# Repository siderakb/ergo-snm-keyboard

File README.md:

# ErgoSNM Keyboard

*ErgoSNM* \- a split ergonomic keyboard integrated with a trackball, designed to encourage people to leave their mouse behind.

- 64 keys in total.
    - Left half 29 + 6 keys.
    - Right half 29 keys + trackball.
- Cherry MX style switches, hot-swap available.
- USB Type-C.
- Column-staggered layout.
- The trackball can replace all mouse operations, allowing your right hand to stay on the *home row*.
    - Cursor movement and scrolling.
    - With the Combos feature:
        - *J*+*K* performs the left click
        - *K*+*L* performs the right click
        - *J*+*L* performs the middle click.

Introduction Video:

| Rev   | MCU                       | Note                                     | Video                                               |
| ----- | ------------------------- | ---------------------------------------- | --------------------------------------------------- |
| `1.x` | Pro Micro (ATmega32U4)    | Experimental version                     |                                                     |
| `2.x` | RaspberryPi **RP2040**    | The first version suitable for daily use | [demo](https://youtu.be/1BXKdrCFn6c)                |
| `3.x` | Nordic **nRF52840** (E73) | First wireless experimental version      | [demo](https://www.youtube.com/watch?v=TtJiaOGiEaQ) |
| `4.x` | ???                       | ⚡In progress                             |                                                     |

Build guide and more information can be found in the [📖Docs](https://siderakb.ziteh.dev/docs/ergosnm/intro)

## Clone

```bash
git clone --recurse-submodules https://github.com/siderakb/ergo-snm-keyboard.git
```

If `key-switches.pretty` folder is empty, run:

```bash
git submodule update --init --recursive
```

## Firmware

- Vial QMK: [siderakb/vial-qmk](https://github.com/siderakb/vial-qmk/tree/siderakb/main/keyboards/siderakb/ergosnm) (*siderakb/main* branch)
- nRF: [siderakb/ergo-snm-nrf-firmware](https://github.com/siderakb/ergo-snm-nrf-firmware)

## License

Hardware available under the [CERN-OHL-P v2](/LICENSE) permissive license.

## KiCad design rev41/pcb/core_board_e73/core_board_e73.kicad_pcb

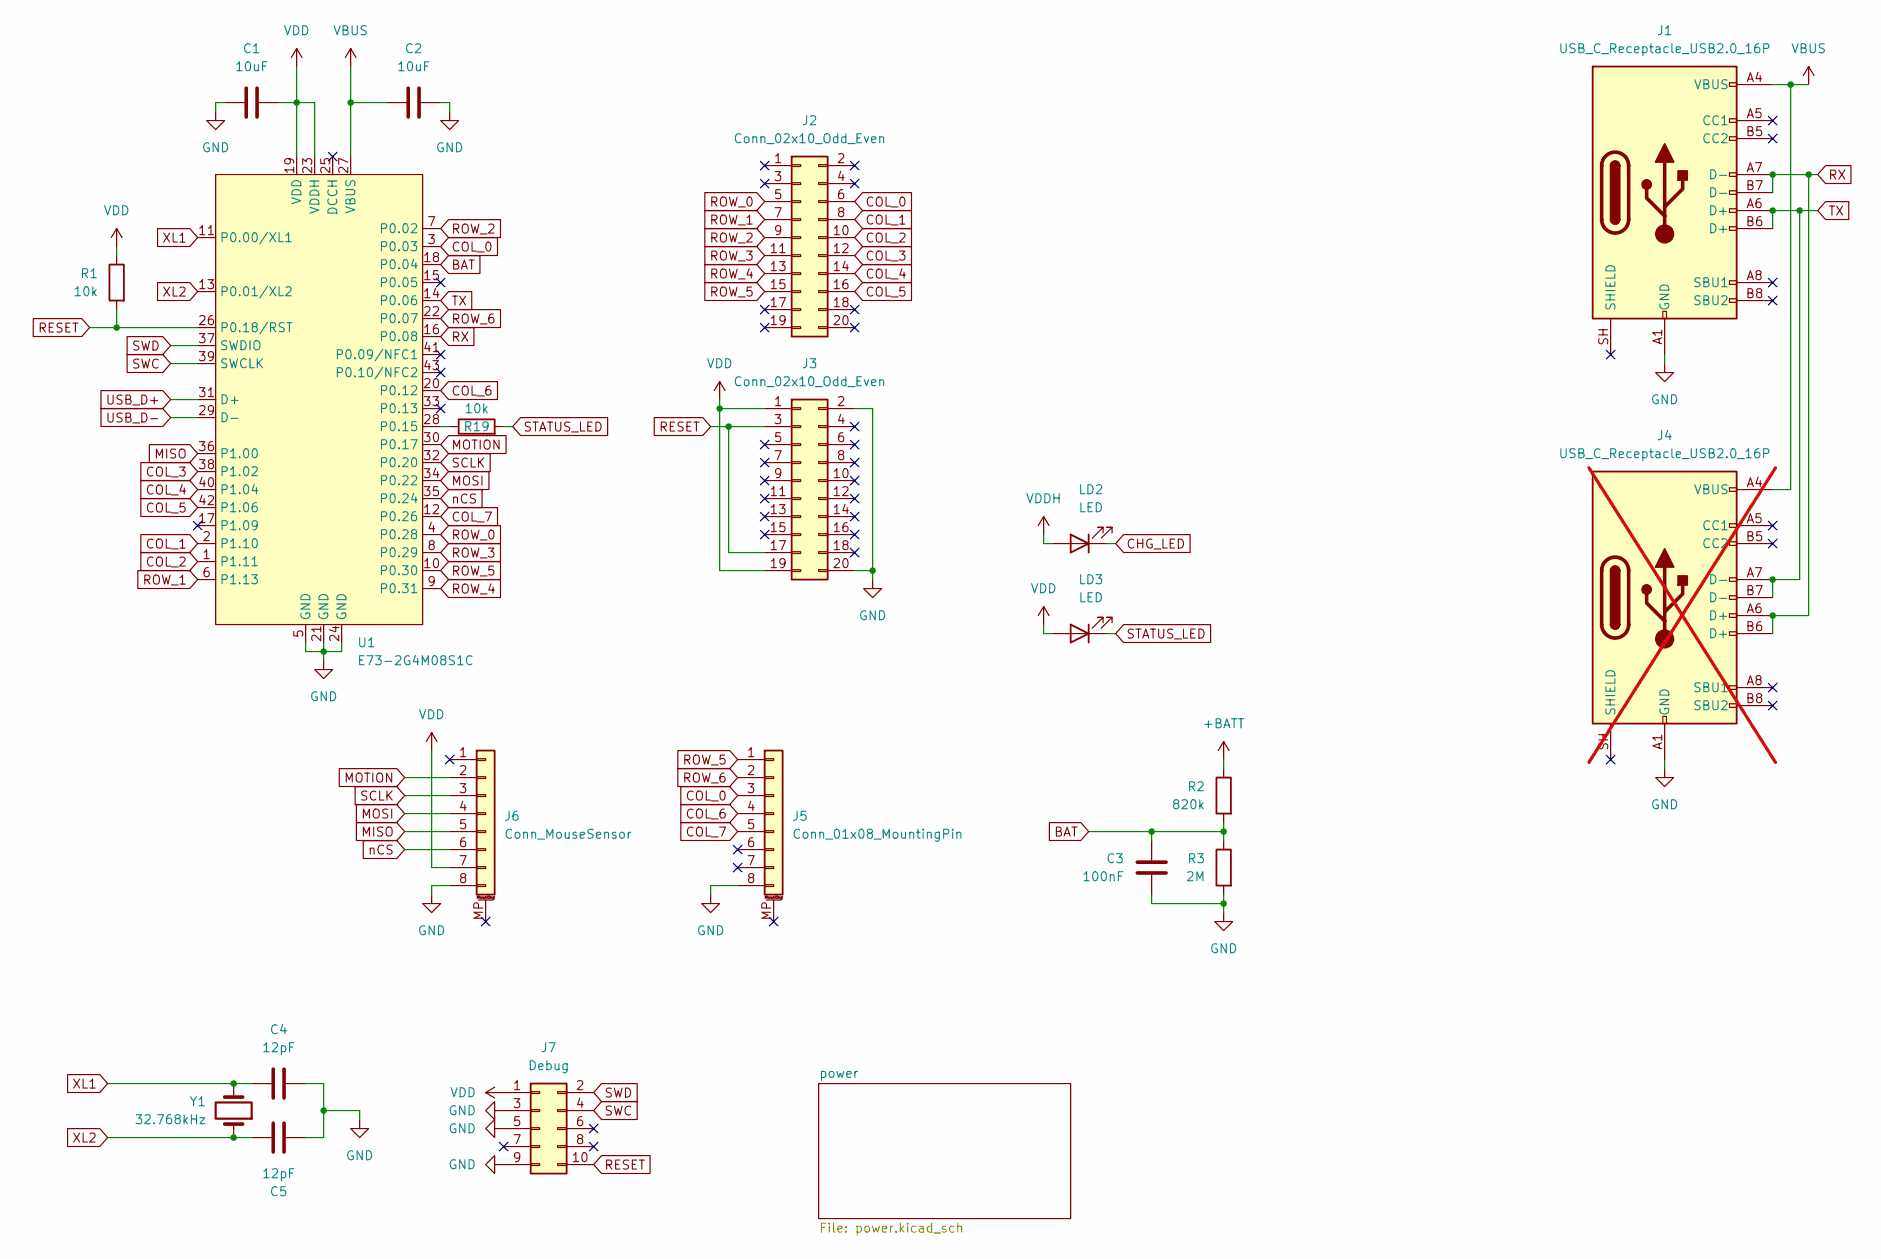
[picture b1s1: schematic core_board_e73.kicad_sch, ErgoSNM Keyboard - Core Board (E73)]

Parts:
C1, C2: 10uF; C_0603_1608Metric; MFR. Part # CL10A106KP8NNNC; JLCPCB Part # C19702
C3: 100nF; C_0402_1005Metric; MFR. Part # CL05B104KO5NNNC; JLCPCB Part # C1525
C4, C5: 12pF; C_0402_1005Metric; MFR. Part # 0402CG120J500NT; JLCPCB Part # C1547
J1: USB_C_Receptacle_USB2.0_16P; USB_C_Receptacle_HRO_TYPE-C-31-M-12; MFR. Part # TYPE-C-31-M-12; JLCPCB Part # C165948
J2, J3: Conn_02x10_Odd_Even; PinHeader_2x10_P1.27mm_Vertical
J4: USB_C_Receptacle_USB2.0_16P; USB_C_Receptacle_HRO_TYPE-C-31-M-12; MFR. Part # TYPE-C-31-M-12; JLCPCB Part # C165948; not fitted
J5: Conn_01x08_MountingPin; FPC_8P_0.5mm_AFC01-S08FCA-00; MFR. Part # FPC-05F-8PH20; JLCPCB Part # C2856797
J6: Conn_MouseSensor; FPC_8P_0.5mm_AFC01-S08FCA-00; MFR. Part # FPC-05F-8PH20; JLCPCB Part # C2856797
J7: Debug; PinHeader_2x05_P1.27mm_Vertical
LD2, LD3: LED; LED_0603_1608Metric_Pad1.05x0.95mm_HandSolder
R1, R19: 10k; R_0402_1005Metric; MFR. Part # 0402WGF1002TCE; JLCPCB Part # C25744
R2: 820k; R_0402_1005Metric; MFR. Part # FRC0402F8203TS; JLCPCB Part # C2909386
R3: 2M; R_0402_1005Metric; MFR. Part # 0402WGF2004TCE; JLCPCB Part # C11512
U1: E73-2G4M08S1C; E73-2G4M08S1C-52840_Hand; MFR. Part # E73-2G4M08S1C; JLCPCB Part # C356849
Y1: 32.768kHz; Crystal_SMD_3215-2Pin_3.2x1.5mm; MFR. Part # Q13FC13500004; JLCPCB Part # C32346

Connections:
+BATT: R2.1; also elsewhere on the board
BAT: C3.1, R2.2, R3.1, U1.18 (P0.04)
CHG_LED: LD2.1 (K); also elsewhere on the board
COL_0: J2.6, J5.3, U1.3 (P0.03)
COL_1: J2.8, U1.2 (P1.10)
COL_2: J2.10, U1.1 (P1.11)
COL_3: J2.12, U1.38 (P1.02)
COL_4: J2.14, U1.40 (P1.04)
COL_5: J2.16, U1.42 (P1.06)
COL_6: J5.4, U1.20 (P0.12)
COL_7: J5.5, U1.12 (P0.26)
GND: C1.1, C2.2, C3.2, C4.2, C5.1, J1.A1 (GND), J1.A12 (GND), J1.B1 (GND), J1.B12 (GND), J3.2, J3.20, J4.A1 (GND), J4.A12 (GND), J4.B1 (GND), J4.B12 (GND), J5.8, J6.8, J7.3, J7.5, J7.9, R3.2, U1.5 (GND), U1.21 (GND), U1.24 (GND); also elsewhere on the board
MISO: J6.5, U1.36 (P1.00)
MOSI: J6.4, U1.34 (P0.22)
MOTION: J6.2, U1.30 (P0.17)
unnamed: R19.1, U1.28 (P0.15)
RESET: J3.3, J3.17, J7.10, R1.2, U1.26 (P0.18/RST)
ROW_0: J2.5, U1.4 (P0.28)
ROW_1: J2.7, U1.6 (P1.13)
ROW_2: J2.9, U1.7 (P0.02)
ROW_3: J2.11, U1.8 (P0.29)
ROW_4: J2.13, U1.9 (P0.31)
ROW_5: J2.15, J5.1, U1.10 (P0.30)
ROW_6: J5.2, U1.22 (P0.07)
RX: J1.A7 (D-), J1.B7 (D-), J4.A6 (D+), J4.B6 (D+), U1.16 (P0.08)
SCLK: J6.3, U1.32 (P0.20)
STATUS_LED: LD3.1 (K), R19.2
SWC: J7.4, U1.39 (SWCLK)
SWD: J7.2, U1.37 (SWDIO)
TX: J1.A6 (D+), J1.B6 (D+), J4.A7 (D-), J4.B7 (D-), U1.14 (P0.06)
USB_D+: U1.31 (D+); also elsewhere on the board
USB_D-: U1.29 (D-); also elsewhere on the board
VBUS: C2.1, J1.A4 (VBUS), J1.A9 (VBUS), J1.B4 (VBUS), J1.B9 (VBUS), J4.A4 (VBUS), J4.A9 (VBUS), J4.B4 (VBUS), J4.B9 (VBUS), U1.27 (VBUS); also elsewhere on the board
VDD: C1.2, J3.1, J3.19, J6.7, J7.1, LD3.2 (A), R1.1, U1.19 (VDD), U1.23 (VDDH); also elsewhere on the board
VDDH: LD2.2 (A); also elsewhere on the board
XL1: C4.1, U1.11 (P0.00/XL1), Y1.2
XL2: C5.2, U1.13 (P0.01/XL2), Y1.1
nCS: J6.6, U1.35 (P0.24)

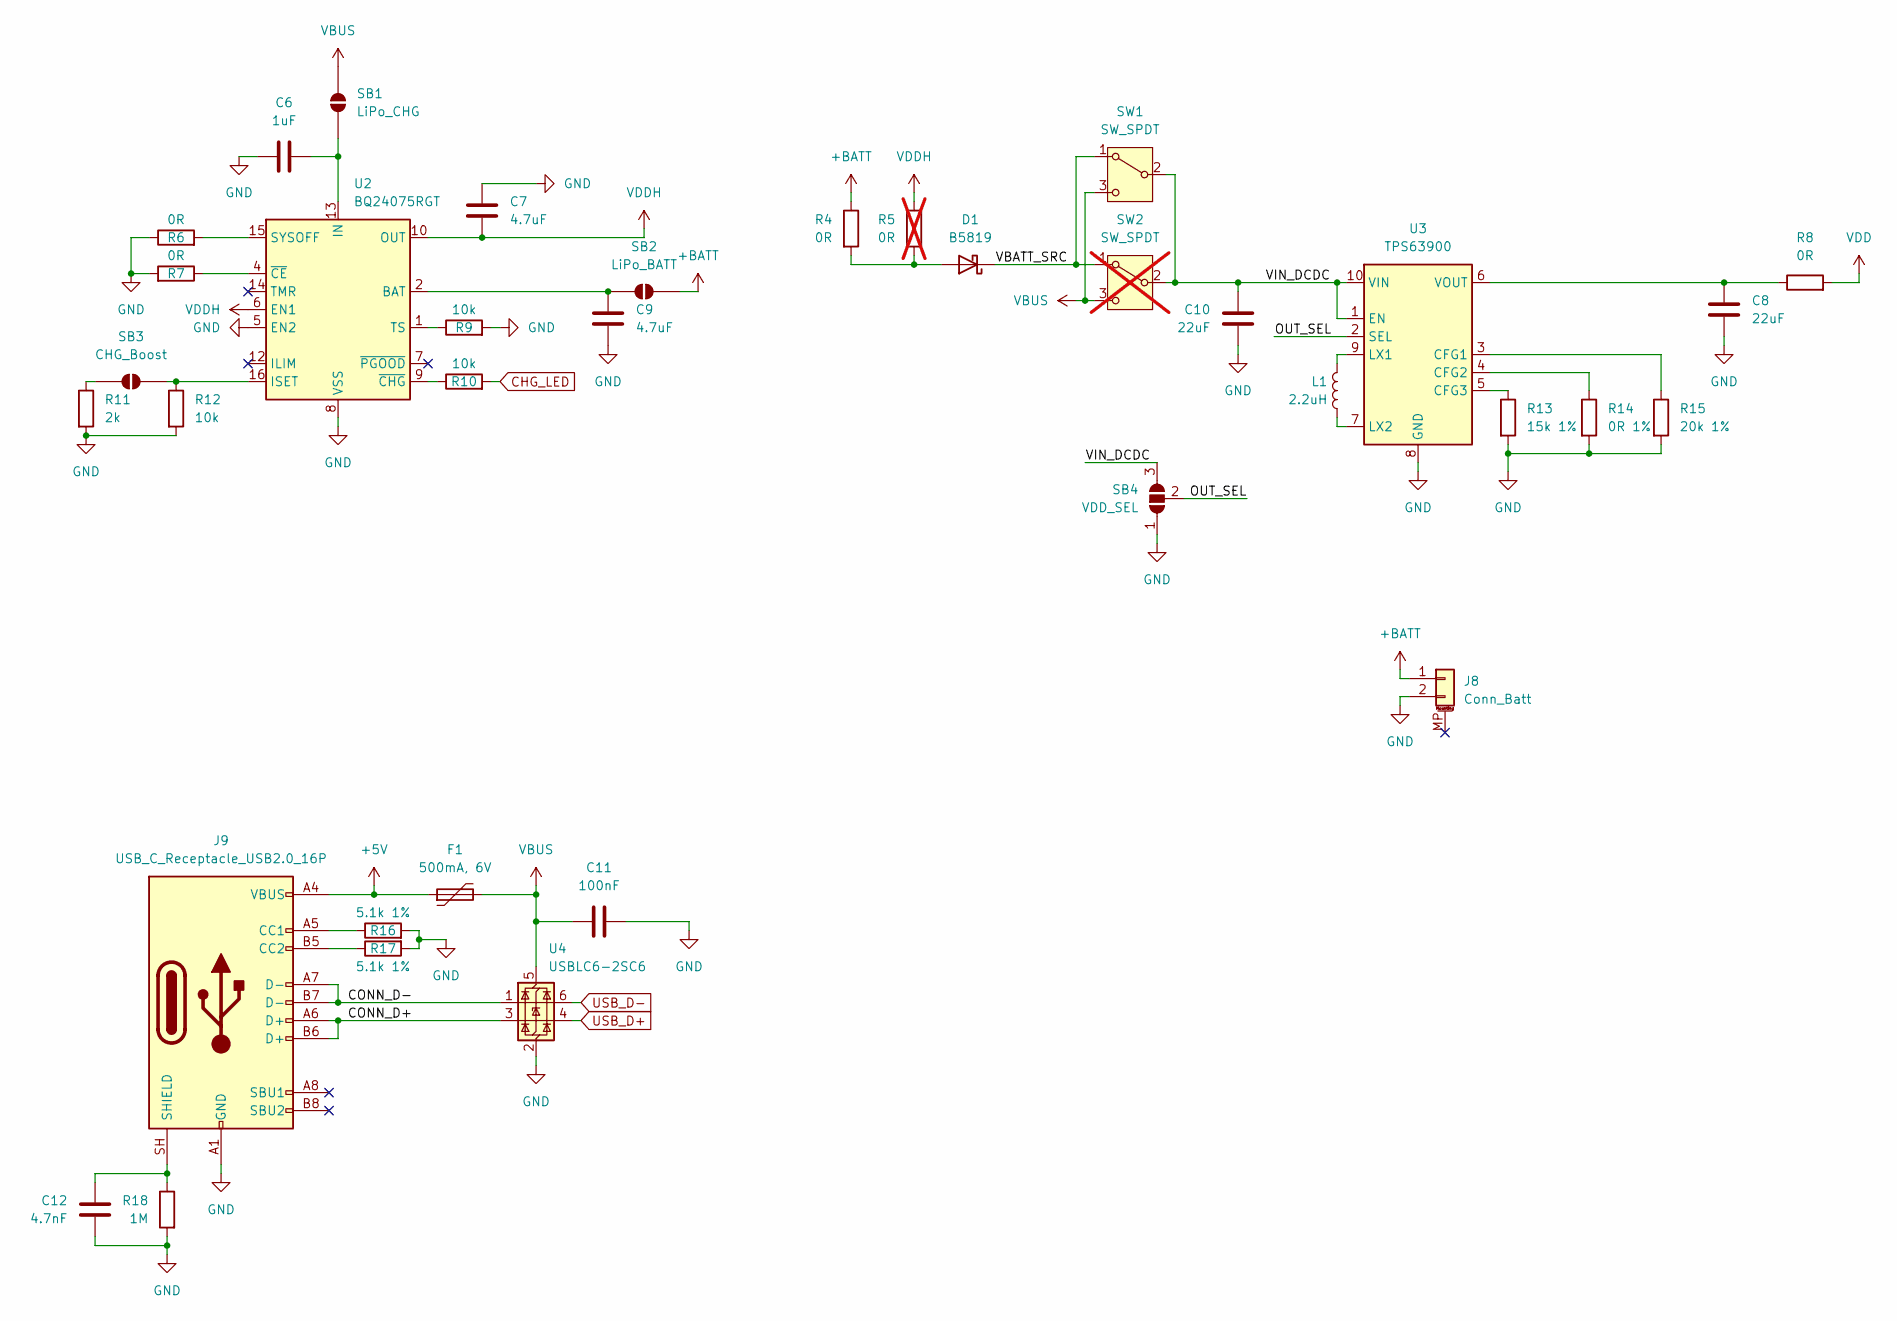
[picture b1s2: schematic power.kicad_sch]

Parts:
C6: 1uF; C_0402_1005Metric; MFR. Part # CL05A105KA5NQNC; JLCPCB Part # C52923
C7, C9: 4.7uF; C_0402_1005Metric; MFR. Part # CL05A475MP5NRNC; JLCPCB Part # C23733
C8, C10: 22uF; C_0805_2012Metric; MFR. Part # CL21A226MAQNNNE; JLCPCB Part # C45783
C11: 100nF; C_0402_1005Metric; MFR. Part # CL05B104KO5NNNC; JLCPCB Part # C1525
C12: 4.7nF; C_0805_2012Metric; MFR. Part # 0805B472K500NT; JLCPCB Part # C1744
D1: B5819; D_SOD-323_HandSoldering; MFR. Part # B5819WS; JLCPCB Part # C64886
F1: 500mA, 6V; Fuse_0805_2012Metric; MFR. Part # SMD0805B050TF; JLCPCB Part # C269104
J8: Conn_Batt; JST_PH_S2B-PH-SM4-TB_1x02-1MP_P2.00mm_Horizontal; MFR. Part # S2B-PH-SM4-TB(LF)(SN); JLCPCB Part # C295747
J9: USB_C_Receptacle_USB2.0_16P; USB_C_Receptacle_HRO_TYPE-C-31-M-12; MFR. Part # TYPE-C-31-M-12; JLCPCB Part # C165948
L1: 2.2uH; L_Changjiang_FNR252012S; MFR. Part # FWP252012P-2R2ML; JLCPCB Part # C5179446
R4, R6, R7, R8: 0R; R_0603_1608Metric; MFR. Part # 0603WAF0000T5E; JLCPCB Part # C21189
R5: 0R; R_0603_1608Metric; MFR. Part # 0603WAF0000T5E; JLCPCB Part # C21189; not fitted
R9, R10, R12: 10k; R_0402_1005Metric; MFR. Part # 0402WGF1002TCE; JLCPCB Part # C25744
R11: 2k; R_0402_1005Metric; MFR. Part # 0402WGF2001TCE; JLCPCB Part # C4109
R13: 15k 1%; R_0603_1608Metric; MFR. Part # 0603WAF1502T5E; JLCPCB Part # C22809
R14: 0R 1%; R_0603_1608Metric; MFR. Part # 0603WAF0000T5E; JLCPCB Part # C21189
R15: 20k 1%; R_0603_1608Metric; MFR. Part # 0603WAF2002T5E; JLCPCB Part # C4184
R16, R17: 5.1k 1%; R_0402_1005Metric; MFR. Part # 0402WGF5101TCE; JLCPCB Part # C25905
R18: 1M; R_0603_1608Metric; MFR. Part # 0603WAF1004T5E; JLCPCB Part # C22935
SB1: LiPo_CHG; SolderJumper-2_P1.3mm_Open_RoundedPad1.0x1.5mm
SB2: LiPo_BATT; SolderJumper-2_P1.3mm_Open_RoundedPad1.0x1.5mm
SB3: CHG_Boost; SolderJumper-2_P1.3mm_Open_RoundedPad1.0x1.5mm
SB4: VDD_SEL; SolderJumper-3_P1.3mm_Open_RoundedPad1.0x1.5mm_NumberLabels
SW1: SW_SPDT; SW_SPDT_SK12D07
SW2: SW_SPDT; SW_SPDT_SK12D07; not fitted
U2: BQ24075RGT; VQFN-16-1EP_3x3mm_P0.5mm_EP1.6x1.6mm; MFR. Part # BQ24075RGTR; JLCPCB Part # C15464
U3: TPS63900; WSON-10-1EP_2.5x2.5mm_P0.5mm_EP1.2x2mm; MFR. Part # TPS63900DSKR; JLCPCB Part # C1518762
U4: USBLC6-2SC6; SOT-23-6; MFR. Part # USBLC6-2SC6; JLCPCB Part # C2687116

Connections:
+5V: F1.1, J9.A4 (VBUS), J9.A9 (VBUS), J9.B4 (VBUS), J9.B9 (VBUS)
+BATT: J8.1, R4.1, SB2.2 (B); also elsewhere on the board
/power/CONN_D+: J9.A6 (D+), J9.B6 (D+), U4.3 (I/O2)
/power/CONN_D-: J9.A7 (D-), J9.B7 (D-), U4.1 (I/O1)
/power/OUT_SEL: SB4.2 (C), U3.2 (SEL)
/power/VBATT_SRC: D1.1 (K), SW1.1 (A), SW2.1 (A)
/power/VIN_DCDC: C10.1, SB4.3 (B), SW1.2 (B), SW2.2 (B), U3.1 (EN), U3.10 (VIN)
CHG_LED: R10.2; also elsewhere on the board
GND: C6.1, C7.1, C8.2, C9.2, C10.2, C11.2, C12.2, J8.2, J9.A1 (GND), J9.A12 (GND), J9.B1 (GND), J9.B12 (GND), R6.1, R7.2, R9.2, R11.2, R12.2, R13.2, R14.2, R15.2, R16.2, R17.2, R18.2, SB4.1 (A), U2.5 (EN2), U2.8 (VSS), U2.17 (VSS), U3.8 (GND), U3.11 (GND), U4.2 (GND); also elsewhere on the board
unnamed: D1.2 (A), R4.2, R5.2
unnamed: J9.A5 (CC1), R16.1
unnamed: J9.B5 (CC2), R17.1
unnamed: C12.1, J9.SH (SHIELD), R18.1
unnamed: C6.2, SB1.1 (A), U2.13 (IN)
unnamed: C9.1, SB2.1 (A), U2.2 (BAT), U2.3 (BAT)
unnamed: R11.1, SB3.1 (A)
unnamed: R12.1, SB3.2 (B), U2.16 (ISET)
unnamed: R6.2, U2.15 (SYSOFF)
unnamed: R9.1, U2.1 (TS)
unnamed: R7.1, U2.4 (~CE)
unnamed: R10.1, U2.9 (~CHG)
unnamed: R15.1, U3.3 (CFG1)
unnamed: R14.1, U3.4 (CFG2)
unnamed: R13.1, U3.5 (CFG3)
unnamed: L1.1, U3.9 (LX1)
unnamed: L1.2, U3.7 (LX2)
unnamed: C8.1, R8.1, U3.6 (VOUT)
USB_D+: U4.4 (I/O2); also elsewhere on the board
USB_D-: U4.6 (I/O1); also elsewhere on the board
VBUS: C11.1, F1.2, SB1.2 (B), SW1.3 (C), SW2.3 (C), U4.5 (VBUS); also elsewhere on the board
VDD: R8.2; also elsewhere on the board
VDDH: C7.2, R5.1, U2.6 (EN1), U2.10 (OUT), U2.11 (OUT); also elsewhere on the board

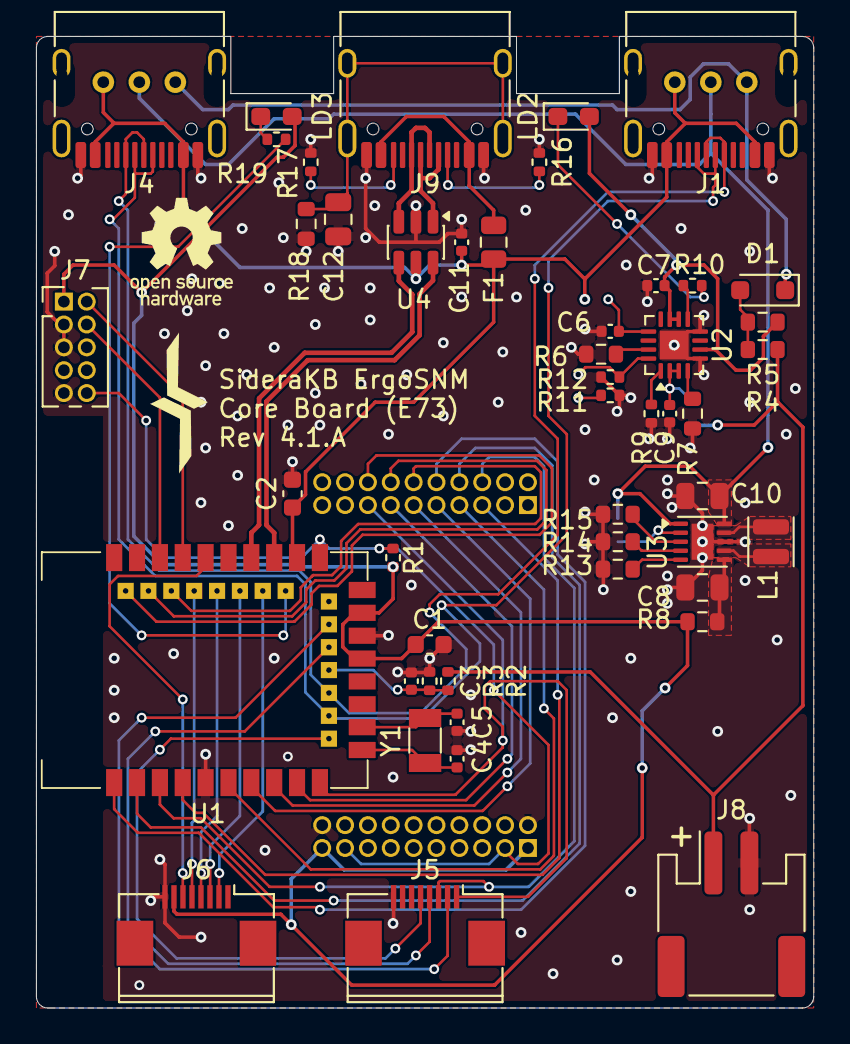
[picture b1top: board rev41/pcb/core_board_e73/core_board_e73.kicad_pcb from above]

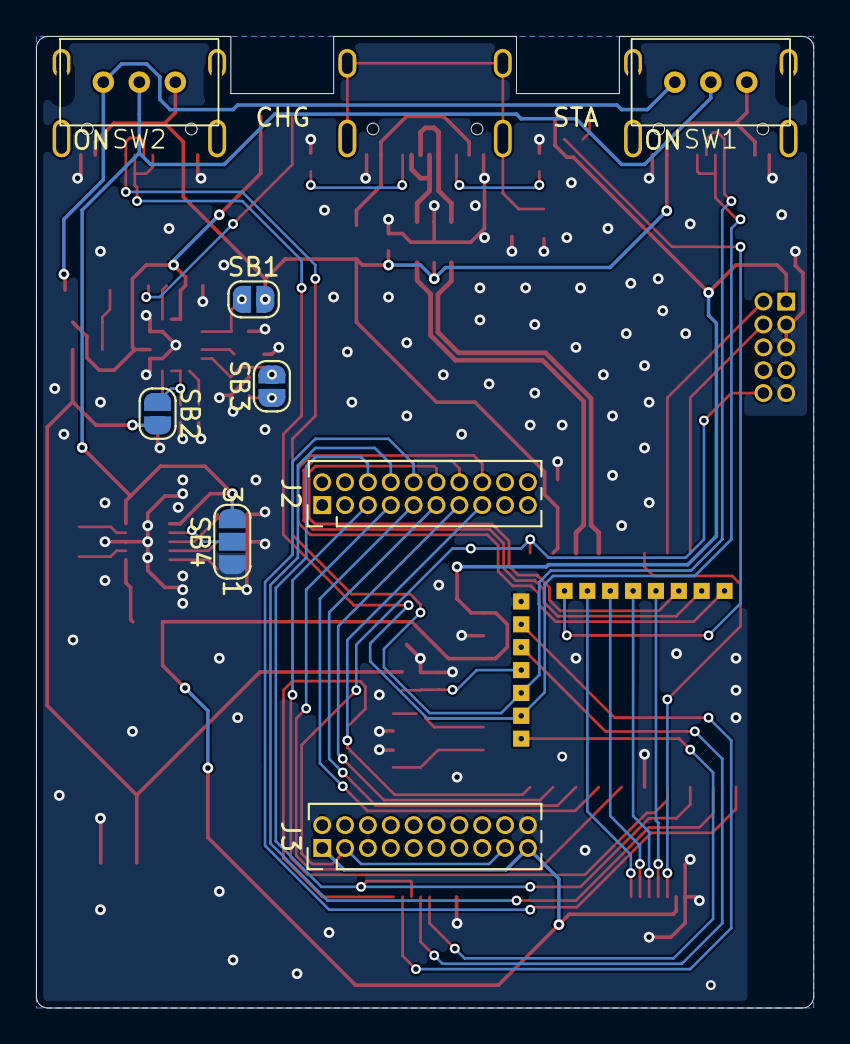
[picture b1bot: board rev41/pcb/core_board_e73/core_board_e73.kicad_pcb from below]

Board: 2 copper layers, 43.2 x 54.0 mm, 56 parts (8 on the bottom side), 62 nets.

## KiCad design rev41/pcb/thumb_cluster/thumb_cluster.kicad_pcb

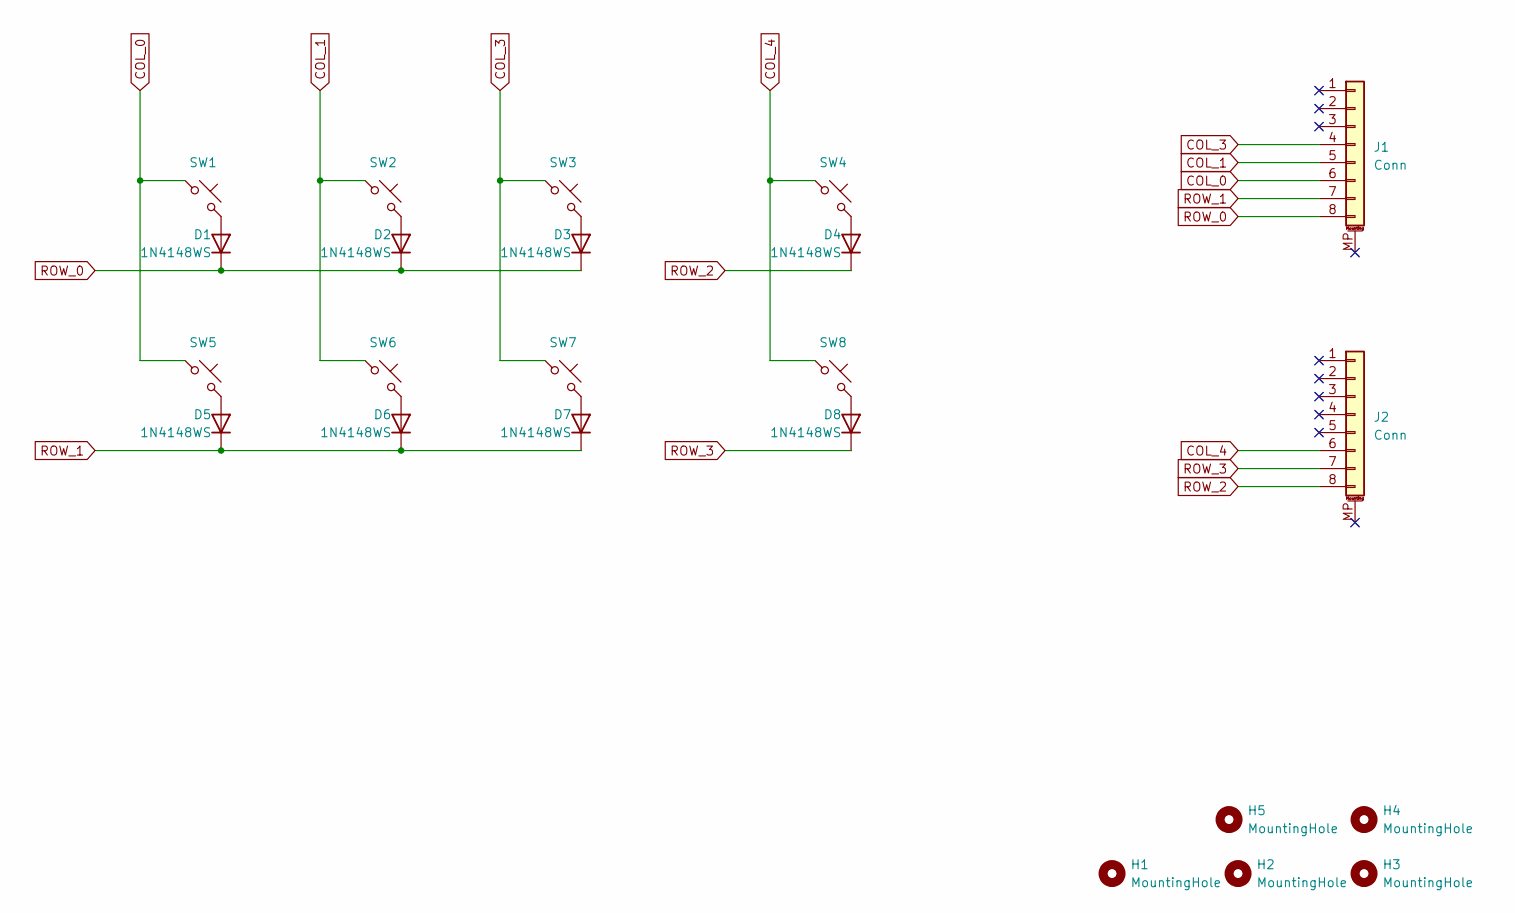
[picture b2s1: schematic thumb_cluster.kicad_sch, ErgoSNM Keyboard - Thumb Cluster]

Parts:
D1, D2, D3, D4, D5, D6, D7, D8: 1N4148WS; D_SOD-323_HandSoldering; MFR. Part # 1N4148WS; JLCPCB Part # C2128
H1, H2, H5: MountingHole; MountingHole_2.2mm_M2_ISO14580
H3, H4: MountingHole; MouseBite-Slot_2.0x4.5mm_inset_D0.5mm_P0.85mm_7h
J1, J2: Conn; FPC_8P_0.5mm_AFC01-S08FCA-00; MFR. Part # FPC-05F-8PH20; JLCPCB Part # C2856797
SW1, SW2, SW3, SW4, SW5, SW6, SW7, SW8: SW_Push_45deg; SW_MX_Kailh_Choc_V1V2_HotSwap_Hybrid_alt1

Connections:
COL_0: J1.6, SW1.1, SW5.1
COL_1: J1.5, SW2.1, SW6.1
COL_3: J1.4, SW3.1, SW7.1
COL_4: J2.6, SW4.1, SW8.1
unnamed: D1.2 (A), SW1.2
unnamed: D2.2 (A), SW2.2
unnamed: D3.2 (A), SW3.2
unnamed: D4.2 (A), SW4.2
unnamed: D5.2 (A), SW5.2
unnamed: D6.2 (A), SW6.2
unnamed: D7.2 (A), SW7.2
unnamed: D8.2 (A), SW8.2
ROW_0: D1.1 (K), D2.1 (K), D3.1 (K), J1.8
ROW_1: D5.1 (K), D6.1 (K), D7.1 (K), J1.7
ROW_2: D4.1 (K), J2.8
ROW_3: D8.1 (K), J2.7

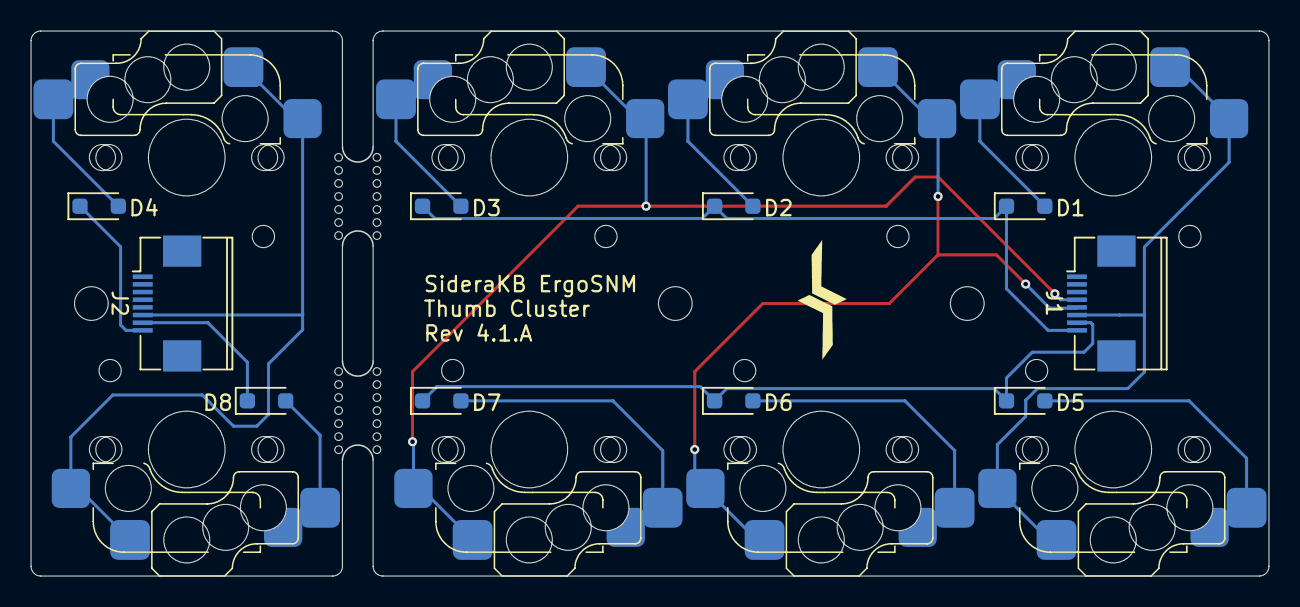
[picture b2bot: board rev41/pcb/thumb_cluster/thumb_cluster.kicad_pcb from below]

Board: 2 copper layers, 80.8 x 35.6 mm, 23 parts (10 on the bottom side), 16 nets.

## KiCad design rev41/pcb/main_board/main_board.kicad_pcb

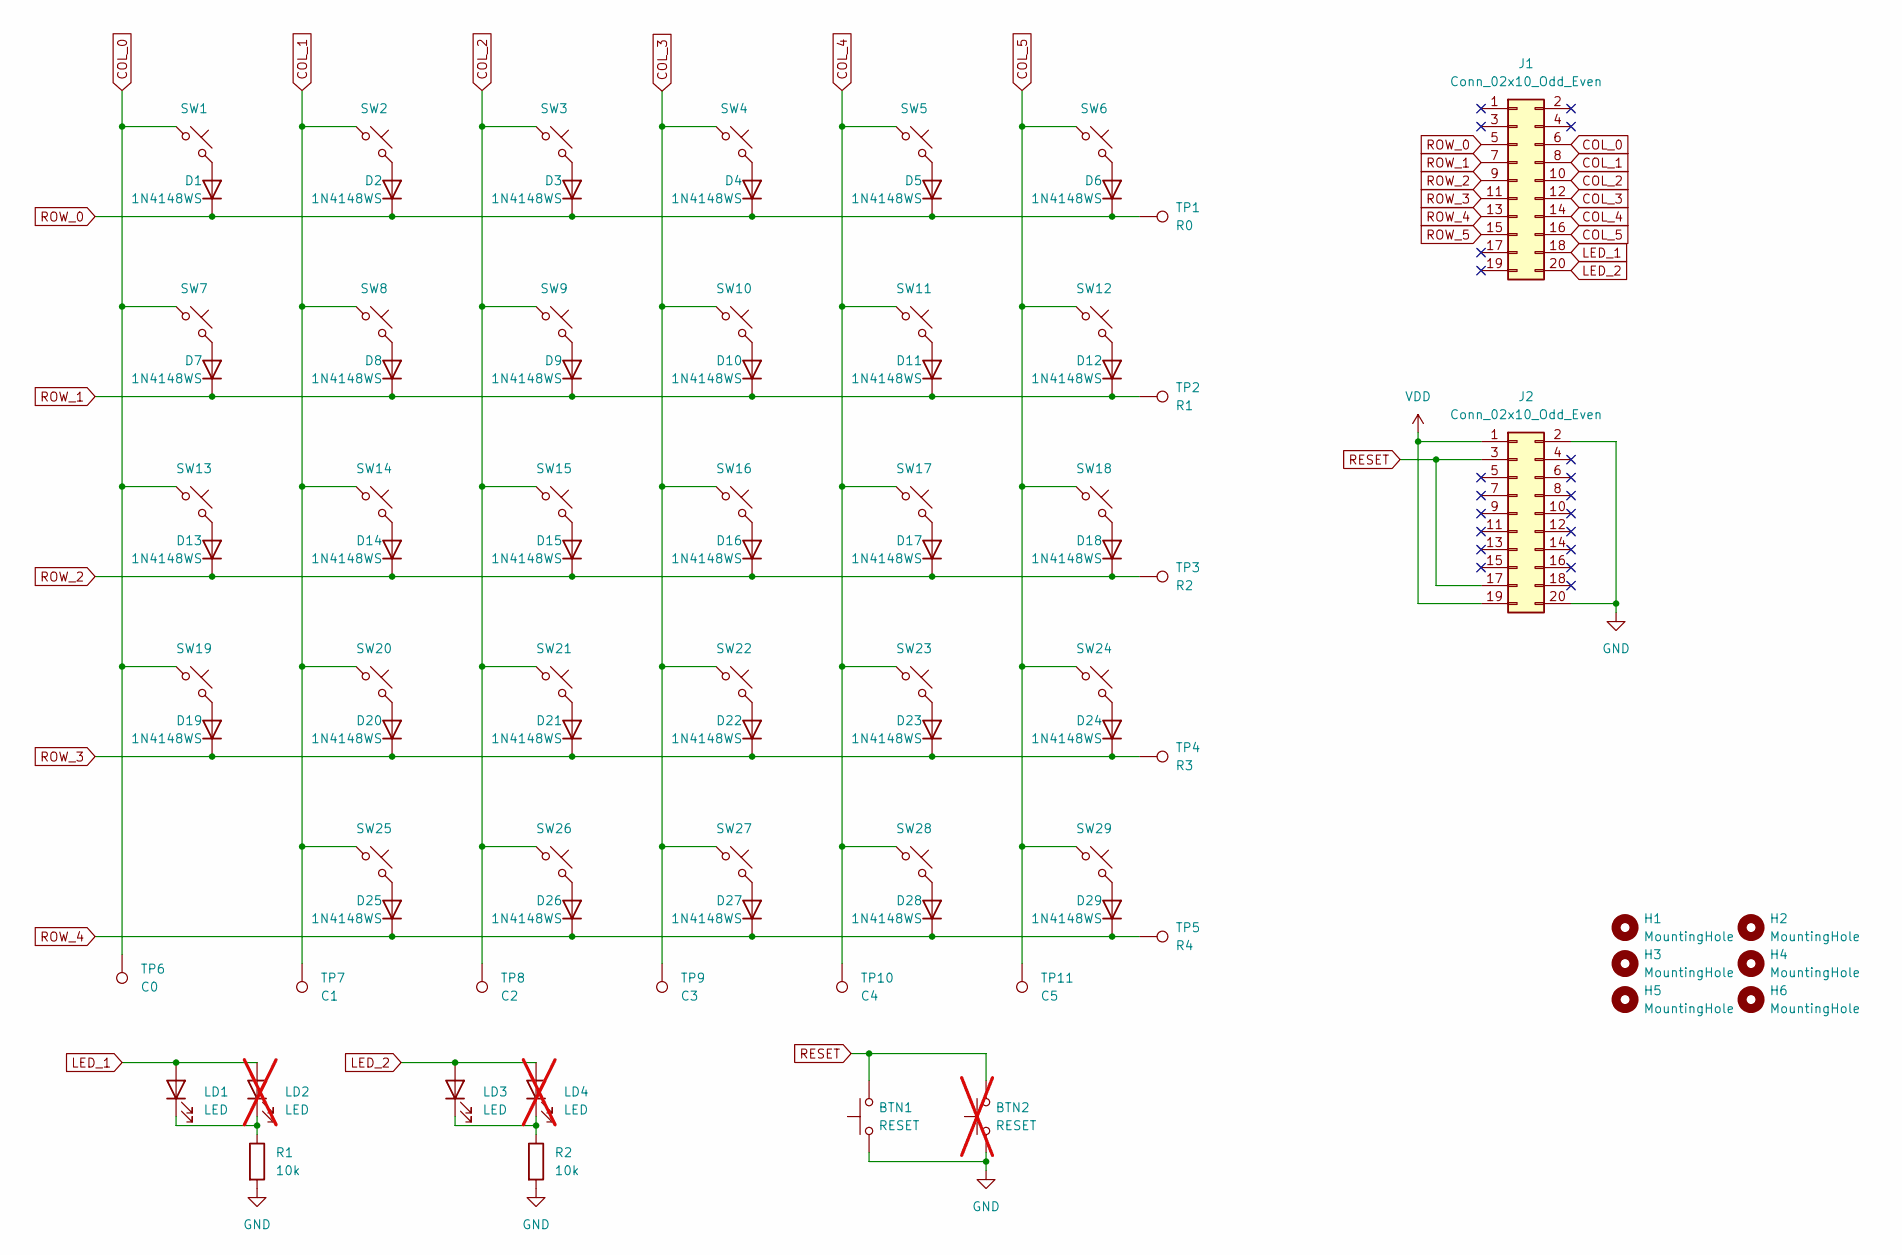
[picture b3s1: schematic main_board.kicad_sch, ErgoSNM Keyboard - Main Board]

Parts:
BTN1: RESET; SW_SPST_TL3342; MFR. Part # TS-1187A-B-A-B; JLCPCB Part # C318884
BTN2: RESET; SW_SPST_TL3342; MFR. Part # TS-1187A-B-A-B; JLCPCB Part # C318884; not fitted
D1, D2, D3, D4, D5, D6, D7, D8, D9, D10, D11, D12, D13, D14, D15, D16, D17, D18, D19, D20, D21, D22, D23, D24, D25, D26, D27, D28, D29: 1N4148WS; D_SOD-323_HandSoldering; MFR. Part # 1N4148WS; JLCPCB Part # C2128
H1, H2, H3, H4, H5, H6: MountingHole; MountingHole_2.2mm_M2_ISO14580
J1, J2: Conn_02x10_Odd_Even; PinSocket_2x10_P1.27mm_Vertical
LD1, LD3: LED; LED_0603_1608Metric
LD2, LD4: LED; LED_0603_1608Metric; not fitted
R1, R2: 10k; R_0402_1005Metric; MFR. Part # 0402WGF1002TCE; JLCPCB Part # C25744
SW1, SW2, SW3, SW4, SW5, SW6, SW7, SW8, SW9, SW10, SW11, SW12, SW13, SW14, SW15, SW16, SW17, SW18, SW19, SW20, SW21, SW22, SW23, SW24, SW25, SW26, SW27, SW28, SW29: SW_Push_45deg; SW_MX_Kailh_Choc_V1V2_HotSwap_Hybrid_double
TP1: R0; TestPoint_Pad_D1.0mm
TP2: R1; TestPoint_Pad_D1.0mm
TP3: R2; TestPoint_Pad_D1.0mm
TP4: R3; TestPoint_Pad_D1.0mm
TP5: R4; TestPoint_Pad_D1.0mm
TP6: C0; TestPoint_Pad_D1.0mm
TP7: C1; TestPoint_Pad_D1.0mm
TP8: C2; TestPoint_Pad_D1.0mm
TP9: C3; TestPoint_Pad_D1.0mm
TP10: C4; TestPoint_Pad_D1.0mm
TP11: C5; TestPoint_Pad_D1.0mm

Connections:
COL_0: J1.6, SW1.1, SW7.1, SW13.1, SW19.1, TP6.1 (1_1)
COL_1: J1.8, SW2.1, SW8.1, SW14.1, SW20.1, SW25.1, TP7.1 (1_1)
COL_2: J1.10, SW3.1, SW9.1, SW15.1, SW21.1, SW26.1, TP8.1 (1_1)
COL_3: J1.12, SW4.1, SW10.1, SW16.1, SW22.1, SW27.1, TP9.1 (1_1)
COL_4: J1.14, SW5.1, SW11.1, SW17.1, SW23.1, SW28.1, TP10.1 (1_1)
COL_5: J1.16, SW6.1, SW12.1, SW18.1, SW24.1, SW29.1, TP11.1 (1_1)
GND: BTN1.1, BTN2.1, J2.2, J2.20, R1.2, R2.2
LED_1: J1.18, LD1.2 (A), LD2.2 (A)
LED_2: J1.20, LD3.2 (A), LD4.2 (A)
unnamed: D1.2 (A), SW1.2
unnamed: D2.2 (A), SW2.2
unnamed: D3.2 (A), SW3.2
unnamed: D4.2 (A), SW4.2
unnamed: D5.2 (A), SW5.2
unnamed: D6.2 (A), SW6.2
unnamed: D7.2 (A), SW7.2
unnamed: D8.2 (A), SW8.2
unnamed: D9.2 (A), SW9.2
unnamed: D10.2 (A), SW10.2
unnamed: D11.2 (A), SW11.2
unnamed: D12.2 (A), SW12.2
unnamed: D13.2 (A), SW13.2
unnamed: D14.2 (A), SW14.2
unnamed: D15.2 (A), SW15.2
unnamed: D16.2 (A), SW16.2
unnamed: D17.2 (A), SW17.2
unnamed: D18.2 (A), SW18.2
unnamed: D19.2 (A), SW19.2
unnamed: D20.2 (A), SW20.2
unnamed: D21.2 (A), SW21.2
unnamed: D22.2 (A), SW22.2
unnamed: D23.2 (A), SW23.2
unnamed: D24.2 (A), SW24.2
unnamed: D25.2 (A), SW25.2
unnamed: D26.2 (A), SW26.2
unnamed: D27.2 (A), SW27.2
unnamed: D28.2 (A), SW28.2
unnamed: D29.2 (A), SW29.2
unnamed: LD1.1 (K), LD2.1 (K), R1.1
unnamed: LD3.1 (K), LD4.1 (K), R2.1
RESET: BTN1.2, BTN2.2, J2.3, J2.17
ROW_0: D1.1 (K), D2.1 (K), D3.1 (K), D4.1 (K), D5.1 (K), D6.1 (K), J1.5, TP1.1 (1_1)
ROW_1: D7.1 (K), D8.1 (K), D9.1 (K), D10.1 (K), D11.1 (K), D12.1 (K), J1.7, TP2.1 (1_1)
ROW_2: D13.1 (K), D14.1 (K), D15.1 (K), D16.1 (K), D17.1 (K), D18.1 (K), J1.9, TP3.1 (1_1)
ROW_3: D19.1 (K), D20.1 (K), D21.1 (K), D22.1 (K), D23.1 (K), D24.1 (K), J1.11, TP4.1 (1_1)
ROW_4: D25.1 (K), D26.1 (K), D27.1 (K), D28.1 (K), D29.1 (K), J1.13, TP5.1 (1_1)
ROW_5: J1.15
VDD: J2.1, J2.19

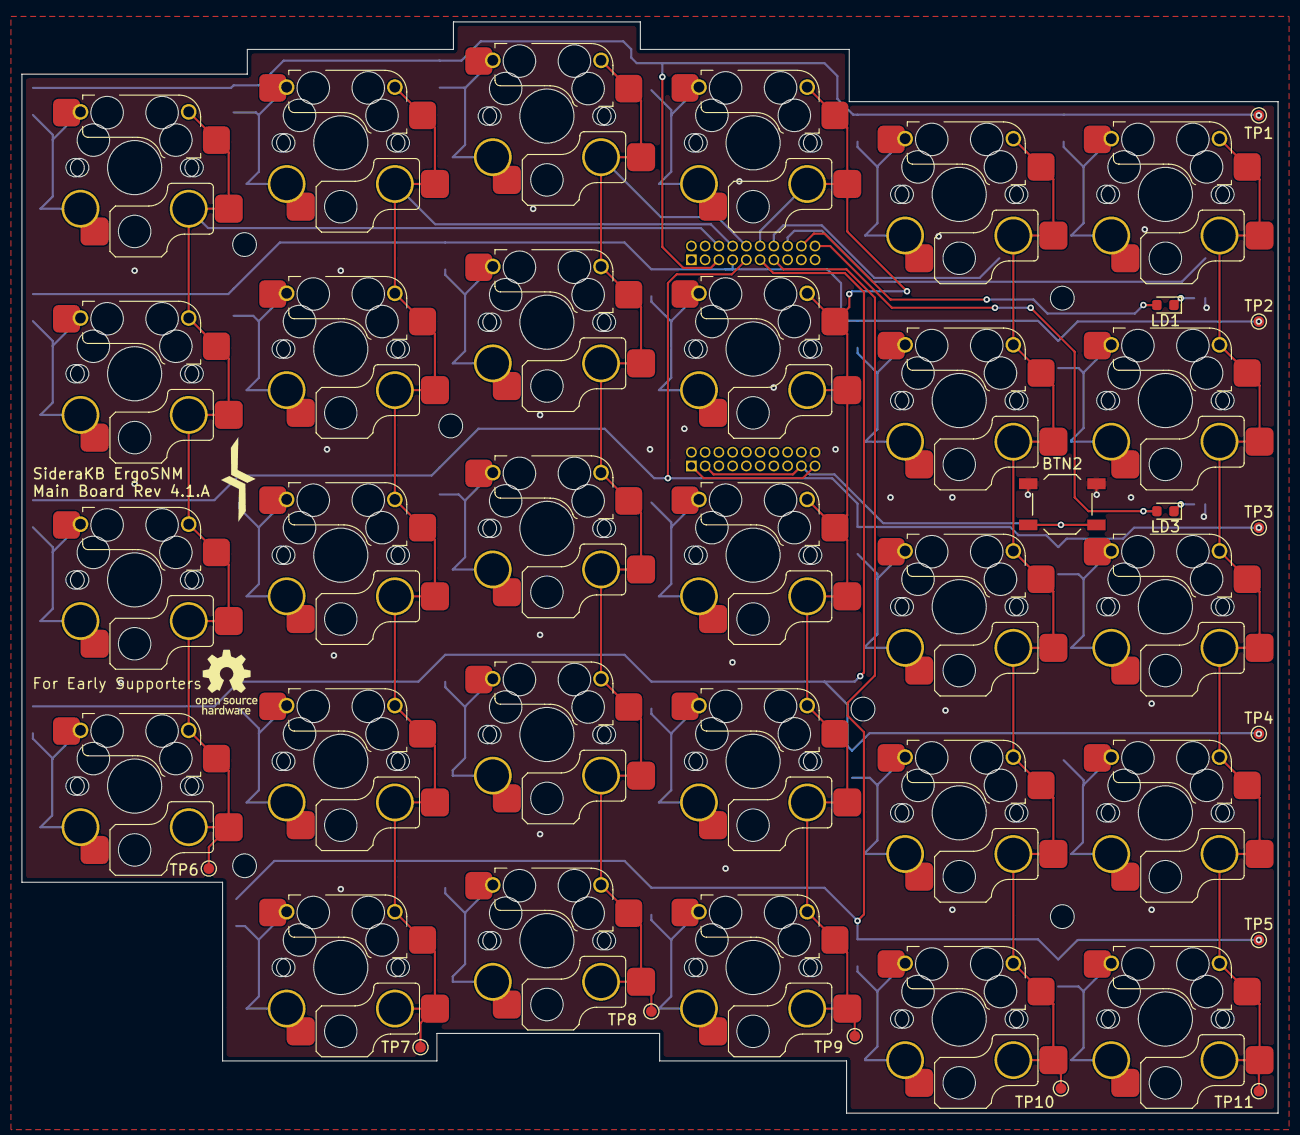
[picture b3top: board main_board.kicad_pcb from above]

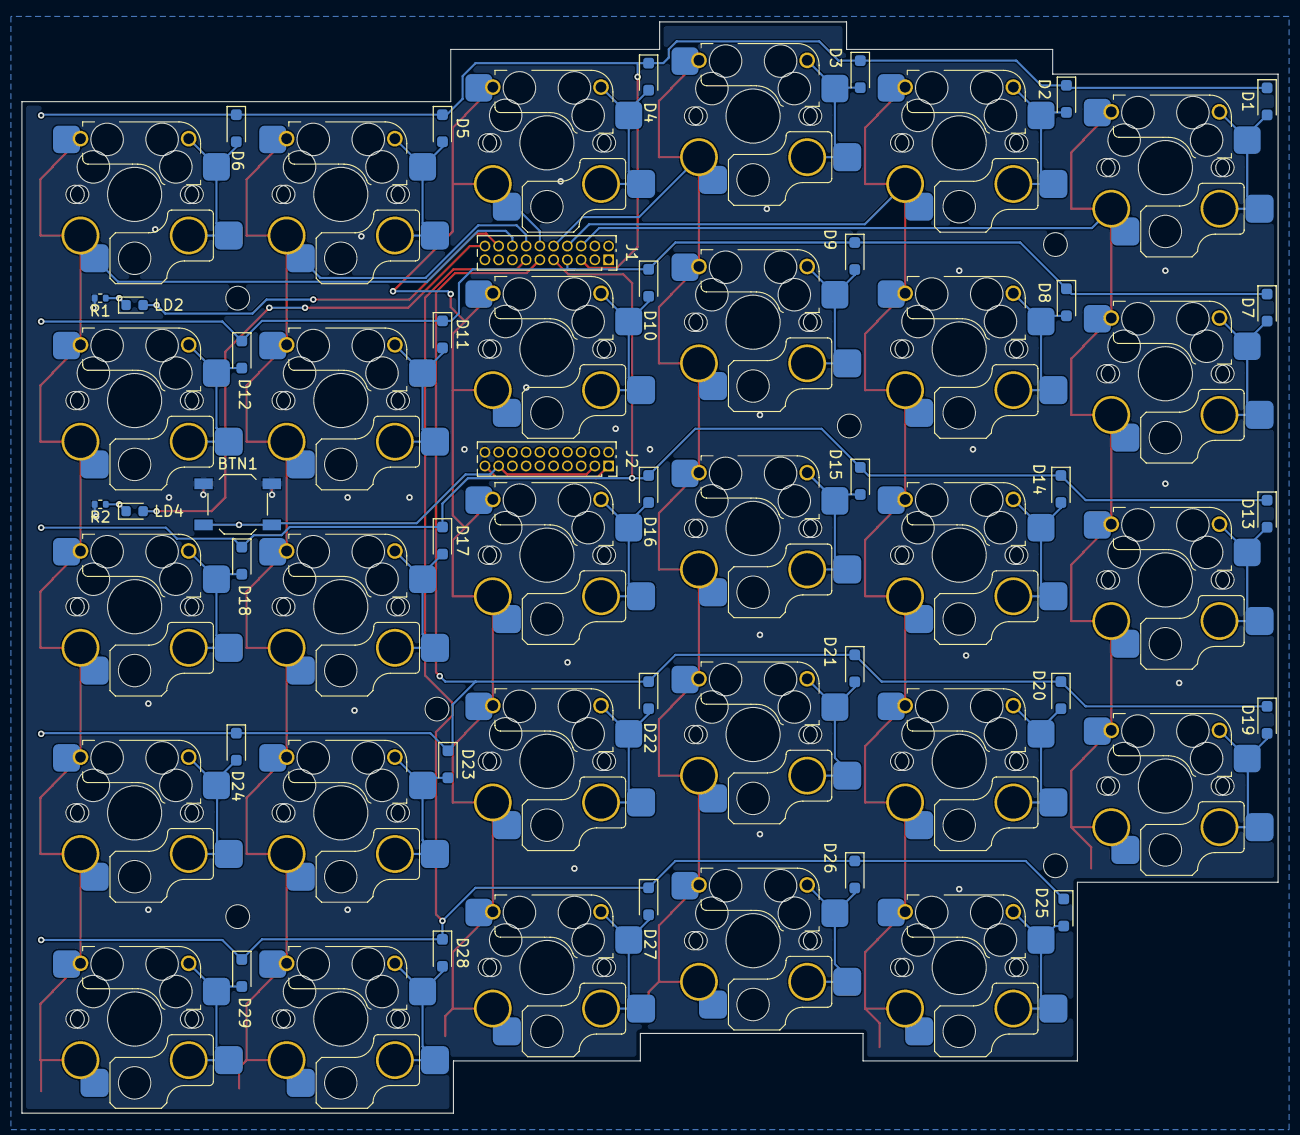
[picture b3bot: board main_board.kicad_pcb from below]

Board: 2 copper layers, 116.1 x 100.8 mm, 85 parts (36 on the bottom side), 47 nets.

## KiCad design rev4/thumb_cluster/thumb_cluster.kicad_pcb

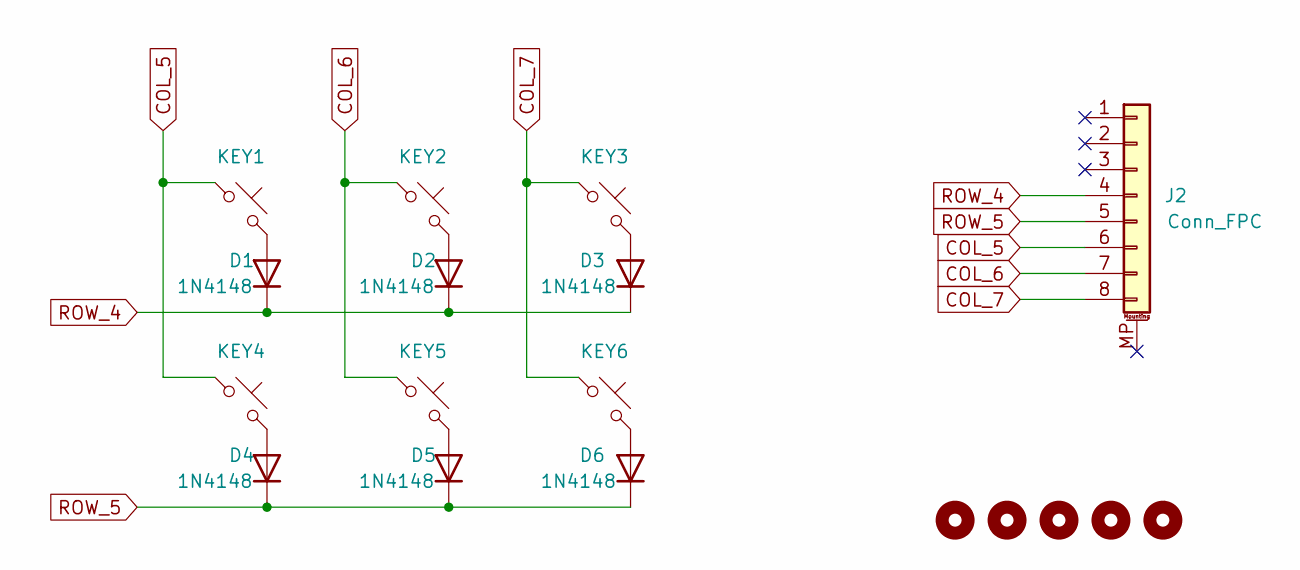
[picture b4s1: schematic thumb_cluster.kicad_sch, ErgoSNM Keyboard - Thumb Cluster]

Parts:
D1, D2, D3, D4, D5, D6: 1N4148; D_SOD-123; MFR. Part # 1N4148W; LCSC C81598
H1, H2, H3, H4, H5: MountingHole; MountingHole_2.2mm_M2
J2: Conn_FPC; FPC_8P_0.5mm_AFC01-S08FCA-00; MFR. Part # AFC01-S08FCA-00; JLCPCB Part # C262657
KEY1, KEY2, KEY3, KEY4, KEY5, KEY6: SW_Push_45deg; SW_MX_Kailh_Choc_V1V2_HotSwap_Hybrid_alt1

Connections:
COL_5: J2.6, KEY1.1, KEY4.1
COL_6: J2.7, KEY2.1, KEY5.1
COL_7: J2.8, KEY3.1, KEY6.1
unnamed: D1.2 (A), KEY1.2
unnamed: D2.2 (A), KEY2.2
unnamed: D3.2 (A), KEY3.2
unnamed: D4.2 (A), KEY4.2
unnamed: D5.2 (A), KEY5.2
unnamed: D6.2 (A), KEY6.2
ROW_4: D1.1 (K), D2.1 (K), D3.1 (K), J2.4
ROW_5: D4.1 (K), D5.1 (K), D6.1 (K), J2.5

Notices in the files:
ErgoSNM_Keyboard/ErgoSNM_keyboard.kicad_sch:
MIT License (Open source hardware)
README.md:
License: CERN-OHL-P v2
rev2/thumb_cluster/thumb_cluster.kicad_sch:
Open source hardware, CERN-OHL-P v2
